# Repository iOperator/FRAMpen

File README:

FRAMpen
Max Gröning
Thomas Bendel
2011, 2012

A project for the MSP430 FRAM challenge for TI Freising interns.

http://processors.wiki.ti.com/index.php/FRAMpen

Files & folders:

doc         Documentation.
firmware    The software for the MSP430FR5739.
pcb         The pcb files. (EAGLE 6)
software    Python script.
README      This file.

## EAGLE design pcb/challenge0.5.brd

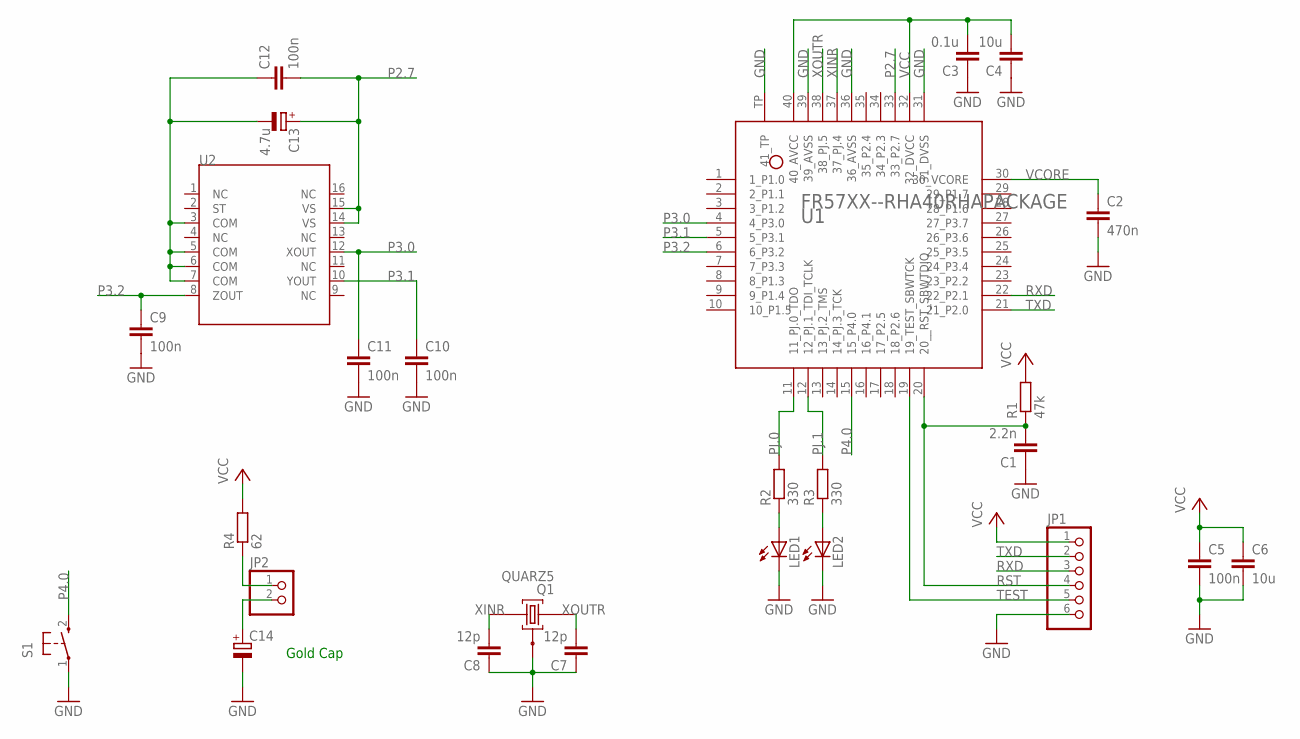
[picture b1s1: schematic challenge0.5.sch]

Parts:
C1: 2.2n; C0805
C2: 470n; C0805
C3: 0.1u; C0805
C4, C6: 10u; C0805
C5, C9, C10, C11, C12: 100n; C0805
C7, C8: 12p; C0805
C13: 4.7u; SMC_A
C14: CPOL-EUE10-20; EB20D
JP1: PINHD-1X6/90; 1X06/90
JP2: PINHD-1X2/90; 1X02/90
LED1, LED2: LEDCHIP-LED0805; CHIP-LED0805
Q1: QUARZ5
R1: 47k; M0805
R2, R3: 330; M0805
R4: 62; R1206
S1: PB; PBTH
U1: FR57XX--RHA40RHAPACKAGE; RHA40
U2: ADXL330; RSA16

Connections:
GND: C1.1, C2.2, C3.1, C4.1, C5.2, C6.2, C7.1, C8.1, C9.2, C10.2, C11.2, C14.-, JP1.6, LED1.C, LED2.C, Q1.GND@0 (0), S1.1, U1.31 (31_DVSS), U1.36 (36_AVSS), U1.39 (39_AVSS), U1.TP (41_TP)
GOLDCAP+1: JP2.1, R4.1
GOLDCAP+2: C14.+, JP2.2
unnamed: C12.1, C13.-, U2.3 (COM), U2.5 (COM), U2.6 (COM), U2.7 (COM)
unnamed: LED1.A, R2.1
unnamed: LED2.A, R3.1
P2.7: C12.2, C13.+, U1.33 (33_P2.7), U2.14 (VS), U2.15 (VS)
P3.0: C11.1, U1.4 (4_P3.0), U2.12 (XOUT)
P3.1: C10.1, U1.5 (5_P3.1), U2.10 (YOUT)
P3.2: C9.1, U1.6 (6_P3.2), U2.8 (ZOUT)
P4.0: S1.2 (S), U1.15 (15_P4.0)
PJ.0: R2.2, U1.11 (11_PJ.0_TDO)
PJ.1: R3.2, U1.12 (12_PJ.1_TDI_TCLK)
RST: C1.2, JP1.4, R1.1, U1.20 (20__RST_SBWTDIO)
RXD: JP1.3, U1.22 (22_P2.1)
TEST: JP1.5, U1.19 (19_TEST_SBWTCK)
TXD: JP1.2, U1.21 (21_P2.0)
VCC: C3.2, C4.2, C5.1, C6.1, JP1.1, R1.2, R4.2, U1.32 (32_DVCC), U1.40 (40_AVCC)
VCORE: C2.1, U1.30 (30_VCORE)
XINR: C8.2, Q1.1, U1.37 (37_PJ.4)
XOUTR: C7.2, Q1.2, U1.38 (38_PJ.5)

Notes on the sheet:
Gold Cap

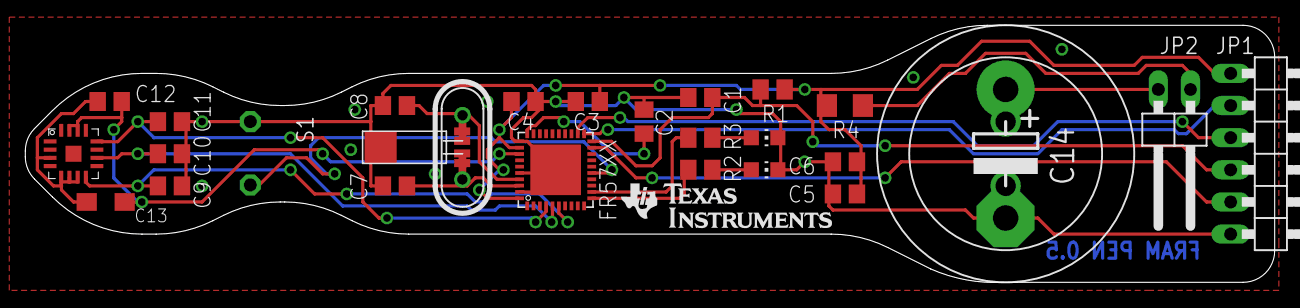
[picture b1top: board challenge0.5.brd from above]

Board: 2 copper layers, 98.7 x 20.3 mm, 27 parts (0 on the bottom side), 21 nets.

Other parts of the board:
U$1: LOGO16_TPLACE

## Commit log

2012-01-16 firmware: LPM4.5 and more
2012-01-17 firmware: Improved usability (button)
2012-01-17 FRAMpen.py: byte handling
2012-01-18 Software: basic calculations
2012-01-20 Software: FRAMpen2.py - Different approach to process the coordinates test.py - Some sample to speed up development
2012-01-20 Firmware: LED bug fixed
